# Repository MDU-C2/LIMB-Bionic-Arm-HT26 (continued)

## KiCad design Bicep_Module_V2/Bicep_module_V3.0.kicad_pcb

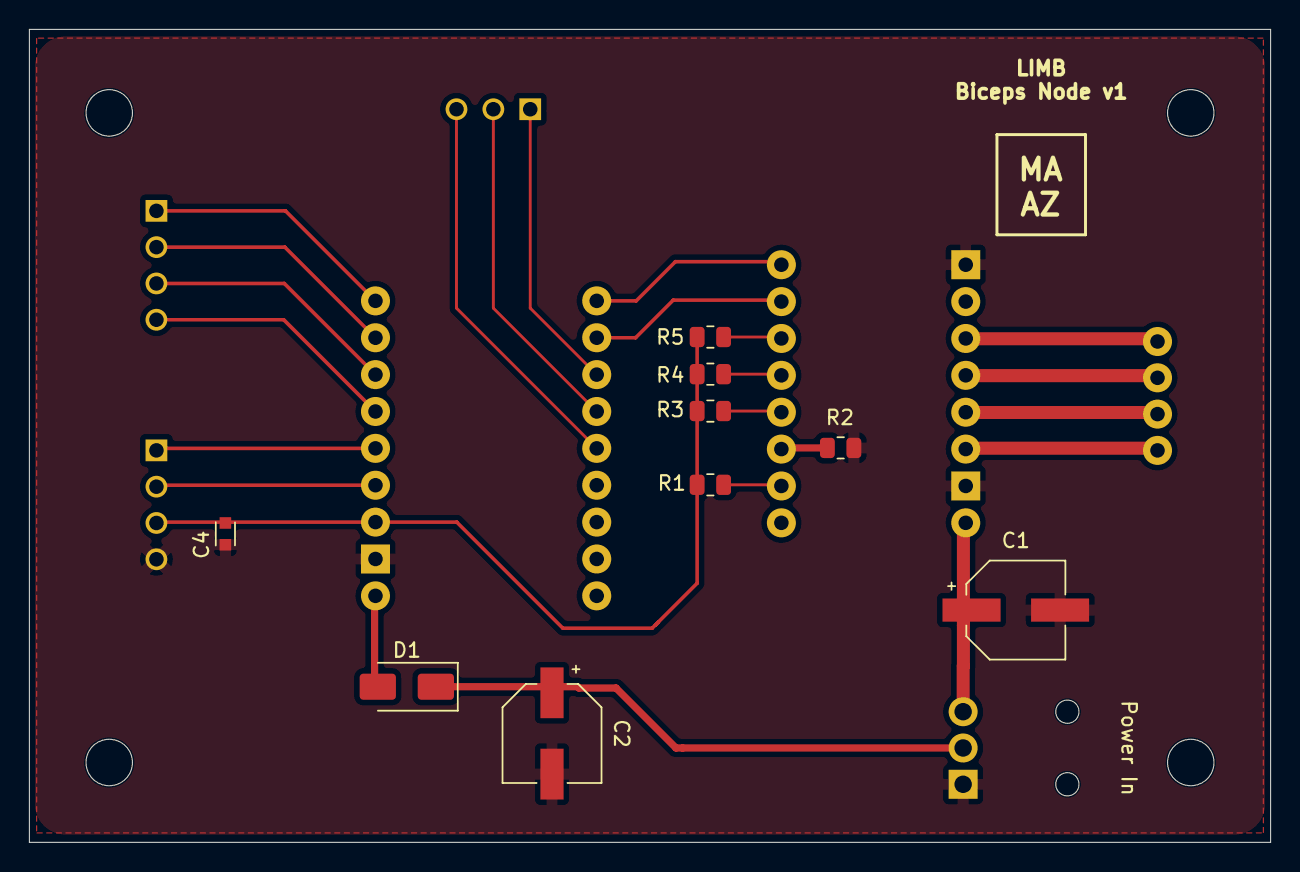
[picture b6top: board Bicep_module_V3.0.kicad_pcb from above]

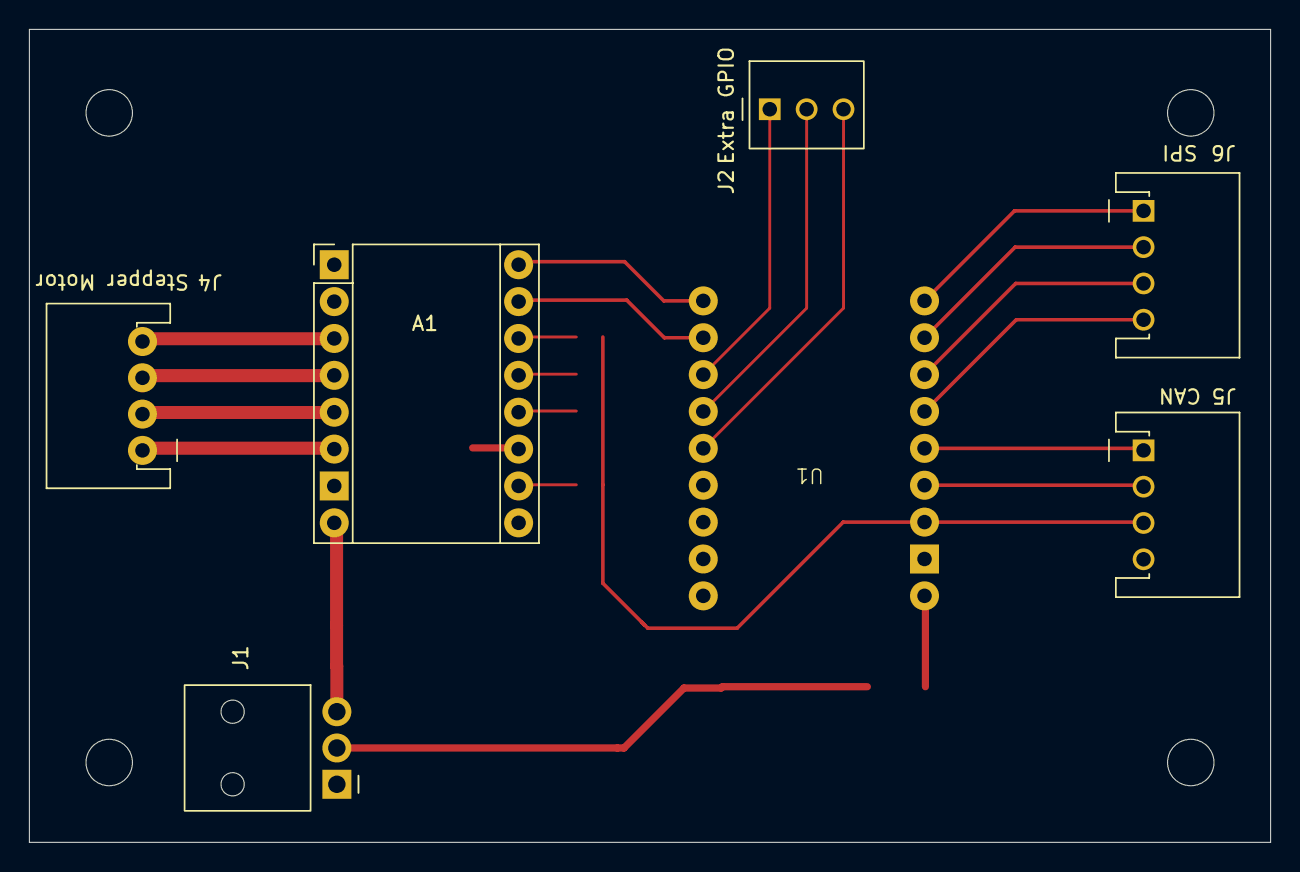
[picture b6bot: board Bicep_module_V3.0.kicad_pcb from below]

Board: 2 copper layers, 85.5 x 56.0 mm, 16 parts (7 on the bottom side), 25 nets.

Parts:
A1: Pololu_Breakout_DRV8825; Pololu_Breakout-16_15.2x20.3mm
C1, C2: 100 uF; CP_Wurth_WCAP-ASLI-D6.3L7.7
C4: 100nF; C_Wurth_WCAP-CSGP-0603_R
D1: D_Schottky; D_SMA
J1: Power In; J_Wurth_WR-NPC2_626003110201
J2: Extra GPIO; J_Wurth_WR-WTB_61900311121
J4: Stepper Motor; J_Wurth_WR-WTB_68800411722
J5: CAN; J_Wurth_WR-WTB_68800411722
J6: SPI; J_Wurth_WR-WTB_68800411722
R1, R2, R3, R4, R5: 10K; R_0805_2012Metric
U1: ESP32-C3-Zero; ESP32-C3-Zero_THT

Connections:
+3.3V: C4.2, J5.3, R1.1, R3.1, R4.1, R5.1, U1.3 (3V3)
+5V: C2.1, D1.1 (K), J1.2
+24V: A1.8 (VMOT), C1.1, J1.3
GND: A1.1 (GND), A1.7 (GND), C1.2, C2.2, C4.1, J1.1, J5.4, R2.1, U1.2 (GND)
MISO: J6.1, U1.9 (GPIO5)
MOSI: J6.2, U1.8 (GPIO4)
unnamed: A1.4 (A1), J4.3
unnamed: A1.3 (A2), J4.4
unnamed: A1.5 (B1), J4.2
unnamed: A1.6 (B2), J4.1
unnamed: A1.10 (M0), R1.2
unnamed: A1.11 (M1), R2.2
unnamed: A1.12 (M2), R3.2
unnamed: A1.13 (~RST), R4.2
unnamed: A1.14 (~SLP), R5.2
unnamed: D1.2 (A), U1.1 (5V)
unnamed: J2.1, U1.12 (GPIO8)
unnamed: J2.2, U1.13 (GPIO9)
unnamed: J2.3, U1.14 (GPIO10)
Rx: J5.2, U1.4 (GPIO0)
SCK: J6.4, U1.6 (GPIO2)
SS: J6.3, U1.7 (GPIO3)
Step_dir: A1.16 (DIR), U1.10 (GPIO6)
Step_step: A1.15 (STEP), U1.11 (GPIO7)
Tx: J5.1, U1.5 (GPIO1)

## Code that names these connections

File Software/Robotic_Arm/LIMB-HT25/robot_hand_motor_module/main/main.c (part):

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  PINKY_CONFIG_INDEX = 4,
  WRIST_CONFIG_INDEX = 5,

  THUMB_SERVO_GPIO = GPIO_NUM_0,
  INDEX_SERVO_GPIO = GPIO_NUM_1,
  MID_SERVO_GPIO = GPIO_NUM_2,
  RING_SERVO_GPIO = GPIO_NUM_3,
  PINKY_SERVO_GPIO = GPIO_NUM_4,
  TWIST_SERVO_GPIO = GPIO_NUM_5,
};
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// Servo configurations - customize each servo individually
static const servo_config_t s_servo_configs[] = {
    // Thumb servo
    [THUMB_CONFIG_INDEX] = {.gpio_pin = THUMB_SERVO_GPIO,
                            .ledc_channel = LEDC_CHANNEL_0,
                            .max_angle = 30,
                            .min_angle = 0,
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                            .direction = SERVO_DIR_REVERSE,
                            .name = "Thumb"},
    // Index finger
    [INDEX_CONFIG_INDEX] = {.gpio_pin = INDEX_SERVO_GPIO,
                            .ledc_channel = LEDC_CHANNEL_1,
                            .max_angle = 85,
                            .min_angle = 0,
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                             .direction = SERVO_DIR_REVERSE,
                             .name = "Middle"},
    // Ring finger
    [RING_CONFIG_INDEX] = {.gpio_pin = RING_SERVO_GPIO,
                           .ledc_channel = LEDC_CHANNEL_3,
                           .max_angle = 50,
                           .min_angle = 0,
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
